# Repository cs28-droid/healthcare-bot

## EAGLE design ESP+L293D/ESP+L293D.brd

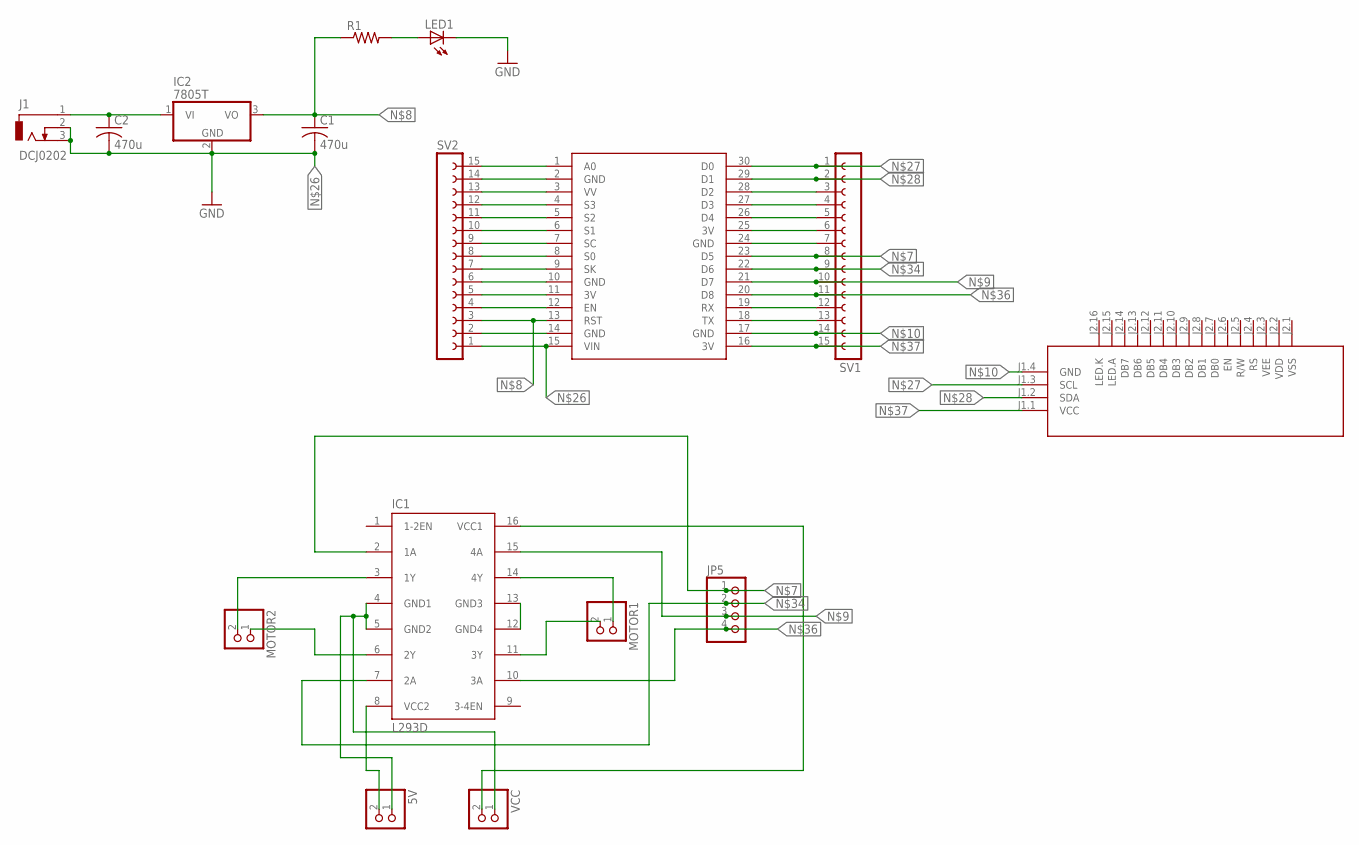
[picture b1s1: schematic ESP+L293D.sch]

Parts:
5V: PINHD-1X2; 1X02
C1, C2: 470u; C025-024X044
IC1: L293D; DIL16
IC2: 7805T; TO220H
J1: DCJ0202
JP5: PINHD-1X4; 1X04
LED1: LEDLD260; LD260
MOTOR1, MOTOR2: PINHD-1X2; 1X02
R1: R-US_0204/5; 0204/5
SV1, SV2: FE15-1; FE15
U$1: NODEMCU
U$2: LCD-I2C-CONVERTER
VCC: PINHD-1X2; 1X02

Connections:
GND: LED1.K (C)
unnamed: IC1.3 (1Y), MOTOR2.2
unnamed: IC1.6 (2Y), MOTOR2.1
unnamed: IC1.14 (4Y), MOTOR1.1
unnamed: IC1.11 (3Y), MOTOR1.2
unnamed: 5V.1, IC1.4 (GND1), IC1.5 (GND2), VCC.1
unnamed: IC1.12 (GND4), IC1.13 (GND3)
unnamed: IC1.2 (1A), JP5.1, SV1.8, U$1.23 (D5)
unnamed: C1.1, IC2.3 (VO), R1.1, SV2.3, U$1.13 (RST)
unnamed: IC1.15 (4A), JP5.3, SV1.10, U$1.21 (D7)
unnamed: SV1.14, U$1.17 (GND), U$2.J1.4 (GND)
unnamed: 5V.2, IC1.8 (VCC2)
unnamed: IC1.16 (VCC1), VCC.2
unnamed: SV2.15, U$1.1 (A0)
unnamed: SV2.14, U$1.2 (GND)
unnamed: SV2.13, U$1.3 (VV)
unnamed: SV2.12, U$1.4 (S3)
unnamed: SV2.11, U$1.5 (S2)
unnamed: SV2.10, U$1.6 (S1)
unnamed: SV2.9, U$1.7 (SC)
unnamed: SV2.8, U$1.8 (S0)
unnamed: SV2.7, U$1.9 (SK)
unnamed: SV2.6, U$1.10 (GND)
unnamed: SV2.5, U$1.11 (3V)
unnamed: SV2.4, U$1.12 (EN)
unnamed: SV2.2, U$1.14 (GND)
unnamed: C1.2, C2.2, IC2.2 (GND), J1.2, J1.3, SV2.1, U$1.15 (VIN)
unnamed: SV1.1, U$1.30 (D0), U$2.J1.3 (SCL)
unnamed: SV1.2, U$1.29 (D1), U$2.J1.2 (SDA)
unnamed: SV1.3, U$1.28 (D2)
unnamed: SV1.4, U$1.27 (D3)
unnamed: SV1.5, U$1.26 (D4)
unnamed: SV1.6, U$1.25 (3V)
unnamed: SV1.7, U$1.24 (GND)
unnamed: IC1.7 (2A), JP5.2, SV1.9, U$1.22 (D6)
unnamed: IC1.10 (3A), JP5.4, SV1.11, U$1.20 (D8)
unnamed: SV1.15, U$1.16 (3V), U$2.J1.1 (VCC)
unnamed: SV1.12, U$1.19 (RX)
unnamed: SV1.13, U$1.18 (TX)
unnamed: C2.1, IC2.1 (VI), J1.1
unnamed: LED1.A, R1.2

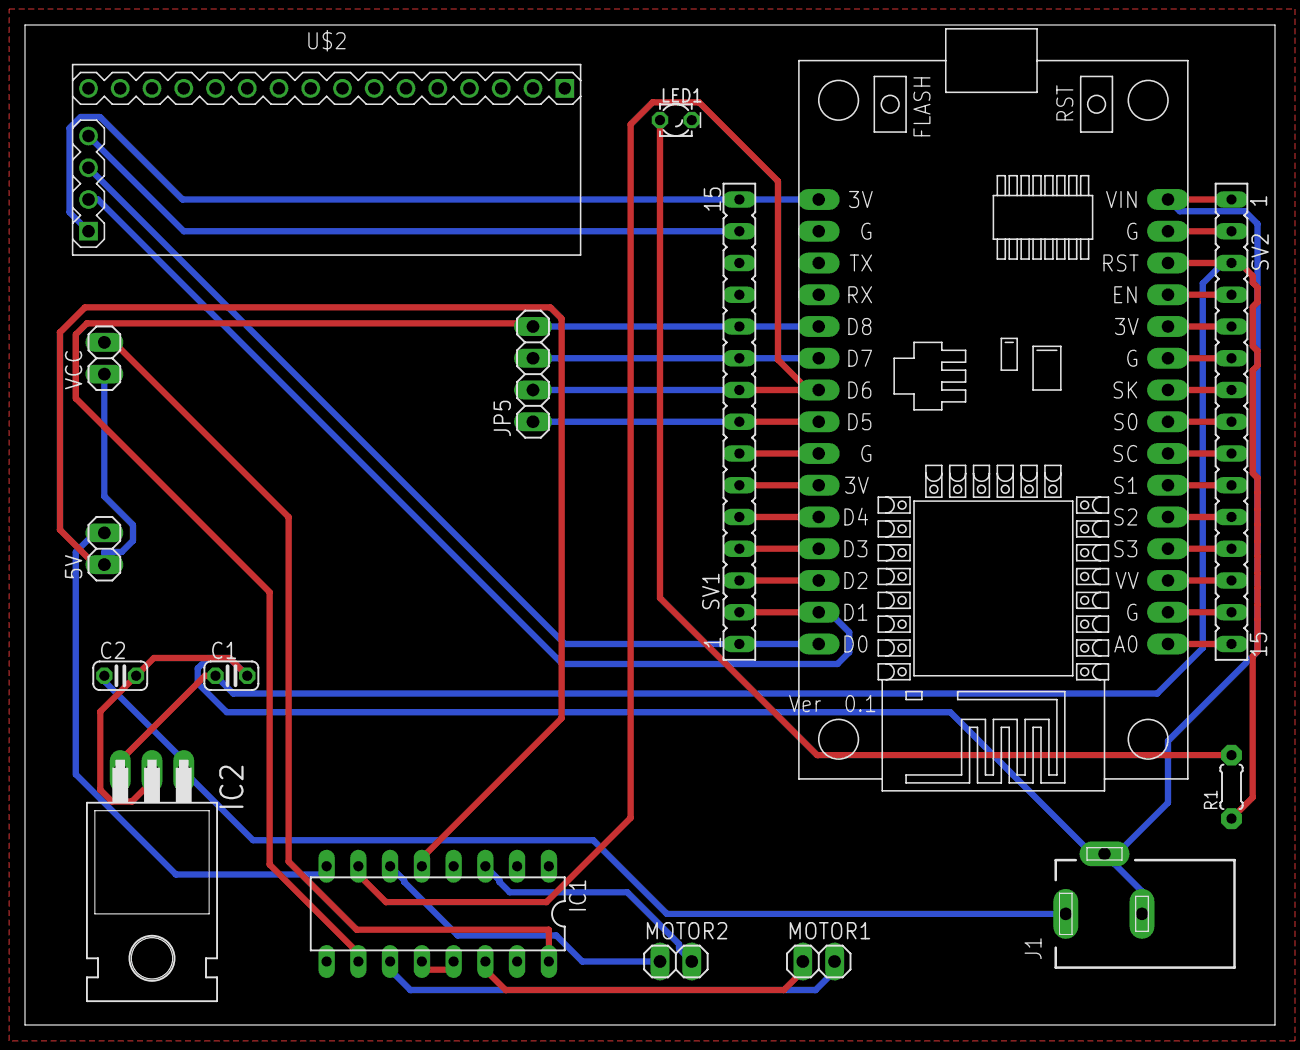
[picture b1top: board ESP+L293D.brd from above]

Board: 2 copper layers, 100.0 x 80.0 mm, 16 parts (0 on the bottom side), 40 nets.

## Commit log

2020-05-26 Create Motor Driver

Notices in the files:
parts and their libraries:
diy-modules: Released under the Creative Commons Attribution 4.0 International License: http://creativecommons.org/licenses/by/4.0
